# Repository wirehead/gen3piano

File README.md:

# gen3piano LED light board

This is a constant current LED driver for 8 20mA LEDs with individual tactile button controls.  This is mostly useful for you if you are either tired of picking out a resistor to drive LEDs at their maximum safe brightness or if you are doing light painting photography.  Both of which apply to me.

]

## First, a story...

Many many years ago now, I had a friend over for my birthday and her husband, who's a semiconductor engineer, gave me some boards he picked up off a random workbench at the office.  Normally this is "Okay, I'm never inviting you over again!" but in their case, they knew I do lightpaintings and stuff and it turns out that, for all of the programmable intelligent whacky lighting things that exist on the marketplace, a little board with a set of LEDs and buttons was a great thing.

Well, I was doing a photoshoot the other day and right towards the end, the 9v battery clip had broken.  And I need to take all of my glow-sticks and figure out which ones are still working and do something there because they were all kinda questionable.  And I had an ancient board made on perfboard that used a header because perfboard-compatible switches are a little tricky to find and I'd left the jumper in place, so the batteries had leaked.

This brought a certain degree of panic.  Because "All of my lights are broken" is a really crappy way to end a shoot that's supposed to be two established artists doing a really cool collaboration.

Ergo, it was time to do some engineering work and solve my problems.

I'm assuming that, if anyone is making boards like the one my friends got me, it's for super-super special people.  Because I searched.

Already stung by breadboard switches, perfboard, and a variety of other concerns, I decided that I should just design a PCB and take advantage of this thing where you can upload the files randomly to some sketchy PCB factory on the internet and get the boards back a few weeks later.

## The CL2 LED driver

I found out about this via a [random google search](http://www.trainelectronics.com/LED_Articles_2007/LED_104/index.htm).

Here's why the CL2N3 is really neat:

 * It's pretty much the same size as the resistor you'd otherwise use.  The middle lead isn't actually used.
 * It's preset and trimmed for 20 mA, so you don't need any more parts.
 * You don't need to figure things out.  You can freely substitute any 20 mA LED.
 * It's a standard through-hole part that's relatively easy to find.  It fits in a breadboard, a perfboard, a manufactured PCB, or whatever random heat-shrink dead-bug freeform circuit you might desire.  (There's a bunch more that are surface-mount)
 * It cares not what voltage you throw at it.  I use 9v batteries but pretty much the voltage drop for the LEDs (somewhere between 1.2v and 4.9v depending on the LED) plus anywhere between 5 and 90v.  

## Why not just use some knobs and some RGB LEDs?

Because the RGB colorspace is a VERY CONVENIENT LIE.

In short, A UV LED will radiate a bunch of visible light that your eye can see.  And you see it as purple.  And it might make things fluoresce a bit.

And then your camera is going to read that as blue, plus whatever colors end up fluorescing.

The same is otherwise true for different spectra.

Also, because it's handy to have 8 little buttons while you are fumbling around in the dark.

## The design

The goal was to fit within the 5cm x 5cm box necessary to get a PCB from DirtyPCB's.

I used [KiCad](http://kicad-pcb.org/).  It seems good enough, actually.

## BOM

 * 8x CL2N3-G (digikey part # CL2N3-G-ND)
 * 8x random 20mA LEDs, generally T 1 3/4 sized a.k.a. 5mm sized.
 * 8x 6mm tactile switches, vaguely Omron B3F-1000 shaped (digikey part # 450-1650-ND)
 * 1x Two terminal, 0.2" spacing terminal blocks, vaguely Molex 39880-030 shaped (Digikey part # ED2580-ND)
 * 1x ceramic 100nF capacitor.
 * 9v battery snaps or other useful power supply
 * This PCB, which you can order via [DirtyPCB's](https://dirtypcbs.com/store/designer/details/wirehead/6309/gen3piano-f-cu-zip) if you so desire.  Or you can fab it yourself via a provider you want.

## Construction

I'm not going to write a tutorial, but here's some pointers:

 * The switches snap in.  And you don't really need to worry about top versus bottom, if they fit, they'll work.
 * The CL2N3-G's should have their flat side matching the silkscreen.  Don't bother soldering the middle lead.
 * The LEDs should have their flat size matching the silk screen.

## Usage

 * Strip the wires for your 9v battery snaps, insert them into the screw-terminals making sure to get the positive in the terminal marked on the silkscreen, and push the buttons.

## Suggested modifications using the same PCB

 * If you solder leads to pins 1 and 3 for each of the switches, you can connect a panel-mount switch.  Or you can solder leads to the two LED pins and use a panel-mount LED or connect up a 20 mA in some sort of random dead-bug fashion.  If you have enough headroom (say, a 9v battery with LEDs that have a 2v drop) you can string a series of LEDs -- but don't try to put LEDs in parallel.

## License

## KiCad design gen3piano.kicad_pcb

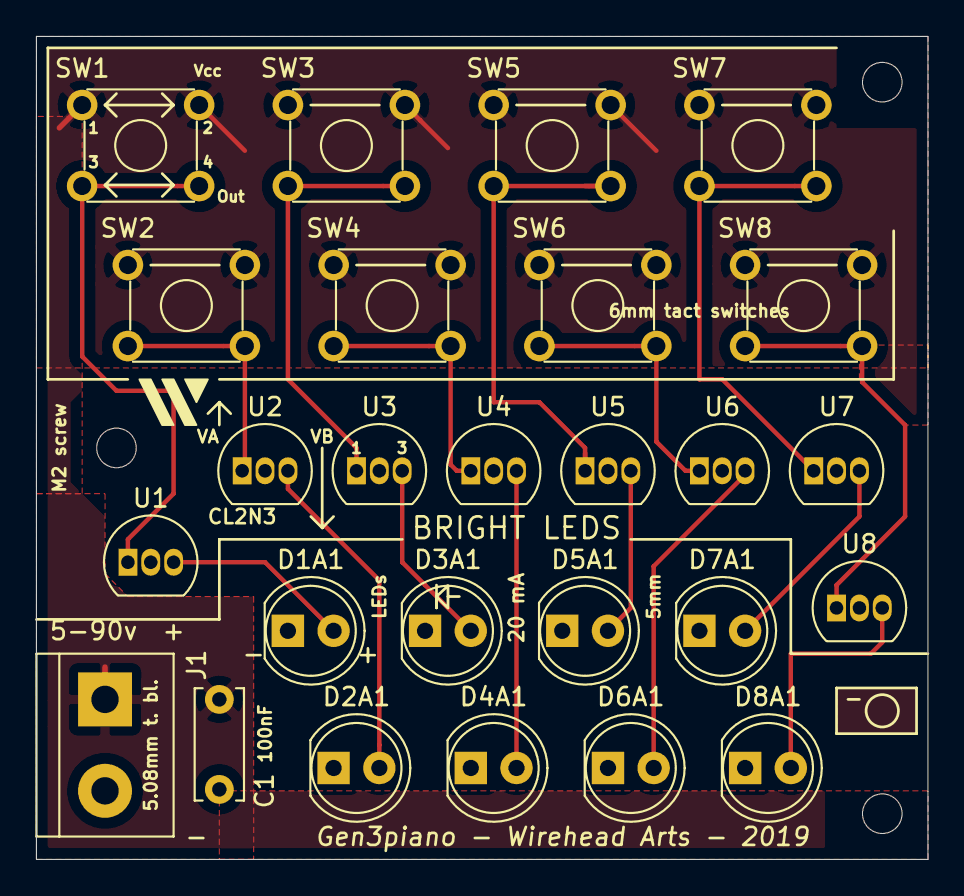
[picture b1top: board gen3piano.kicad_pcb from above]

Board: 2 copper layers, 49.5 x 45.7 mm, 29 parts (0 on the bottom side), 18 nets.

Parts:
C1: 100 nF; C_Disc_D6.0mm_W2.5mm_P5.00mm
D1A1, D2A1, D3A1, D4A1, D5A1, D6A1, D7A1, D8A1: LED; LED_D5.0mm_Clear
J1: Screw_Terminal_01x02; TerminalBlock_bornier-2_P5.08mm
REF1, REF2, REF3: MountingHole_2.2mm_M2
SW1, SW2, SW3, SW4, SW5, SW6, SW7, SW8: SW_Push_Dual; SW_TH_Tactile_Omron_B3F-10xx
U1, U2, U3, U4, U5, U6, U7, U8: CL2N3; TO-92_Inline

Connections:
GND: C1.2, D1A1.1, D2A1.1, D3A1.1, D4A1.1, D5A1.1, D6A1.1, D7A1.1, D8A1.1, J1.2
unnamed: D1A1.2, U1.3
unnamed: D2A1.2, U2.3
unnamed: D3A1.2, U3.3
unnamed: D4A1.2, U4.3
unnamed: D5A1.2, U5.3
unnamed: D6A1.2, U6.3
unnamed: D7A1.2, U7.3
unnamed: D8A1.2, U8.3
unnamed: SW1.3, SW1.4, U1.1
unnamed: SW2.3, SW2.4, U2.1
unnamed: SW3.3, SW3.4, U3.1
unnamed: SW4.3, SW4.4, U4.1
unnamed: SW5.3, SW5.4, U5.1
unnamed: SW6.3, SW6.4, U6.1
unnamed: SW7.3, SW7.4, U7.1
unnamed: SW8.3, SW8.4, U8.1
VCC: C1.1, J1.1, SW1.1, SW1.2, SW2.1, SW2.2, SW3.1, SW3.2, SW4.1, SW4.2, SW5.1, SW5.2, SW6.1, SW6.2, SW7.1, SW7.2, SW8.1, SW8.2

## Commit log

2019-05-04 initial commit.
2019-05-17 update docs, add license and pic.

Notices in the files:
README.md:
License:
[License: CC BY-SA 4.0](https://creativecommons.org/licenses/by-sa/4.0/)
